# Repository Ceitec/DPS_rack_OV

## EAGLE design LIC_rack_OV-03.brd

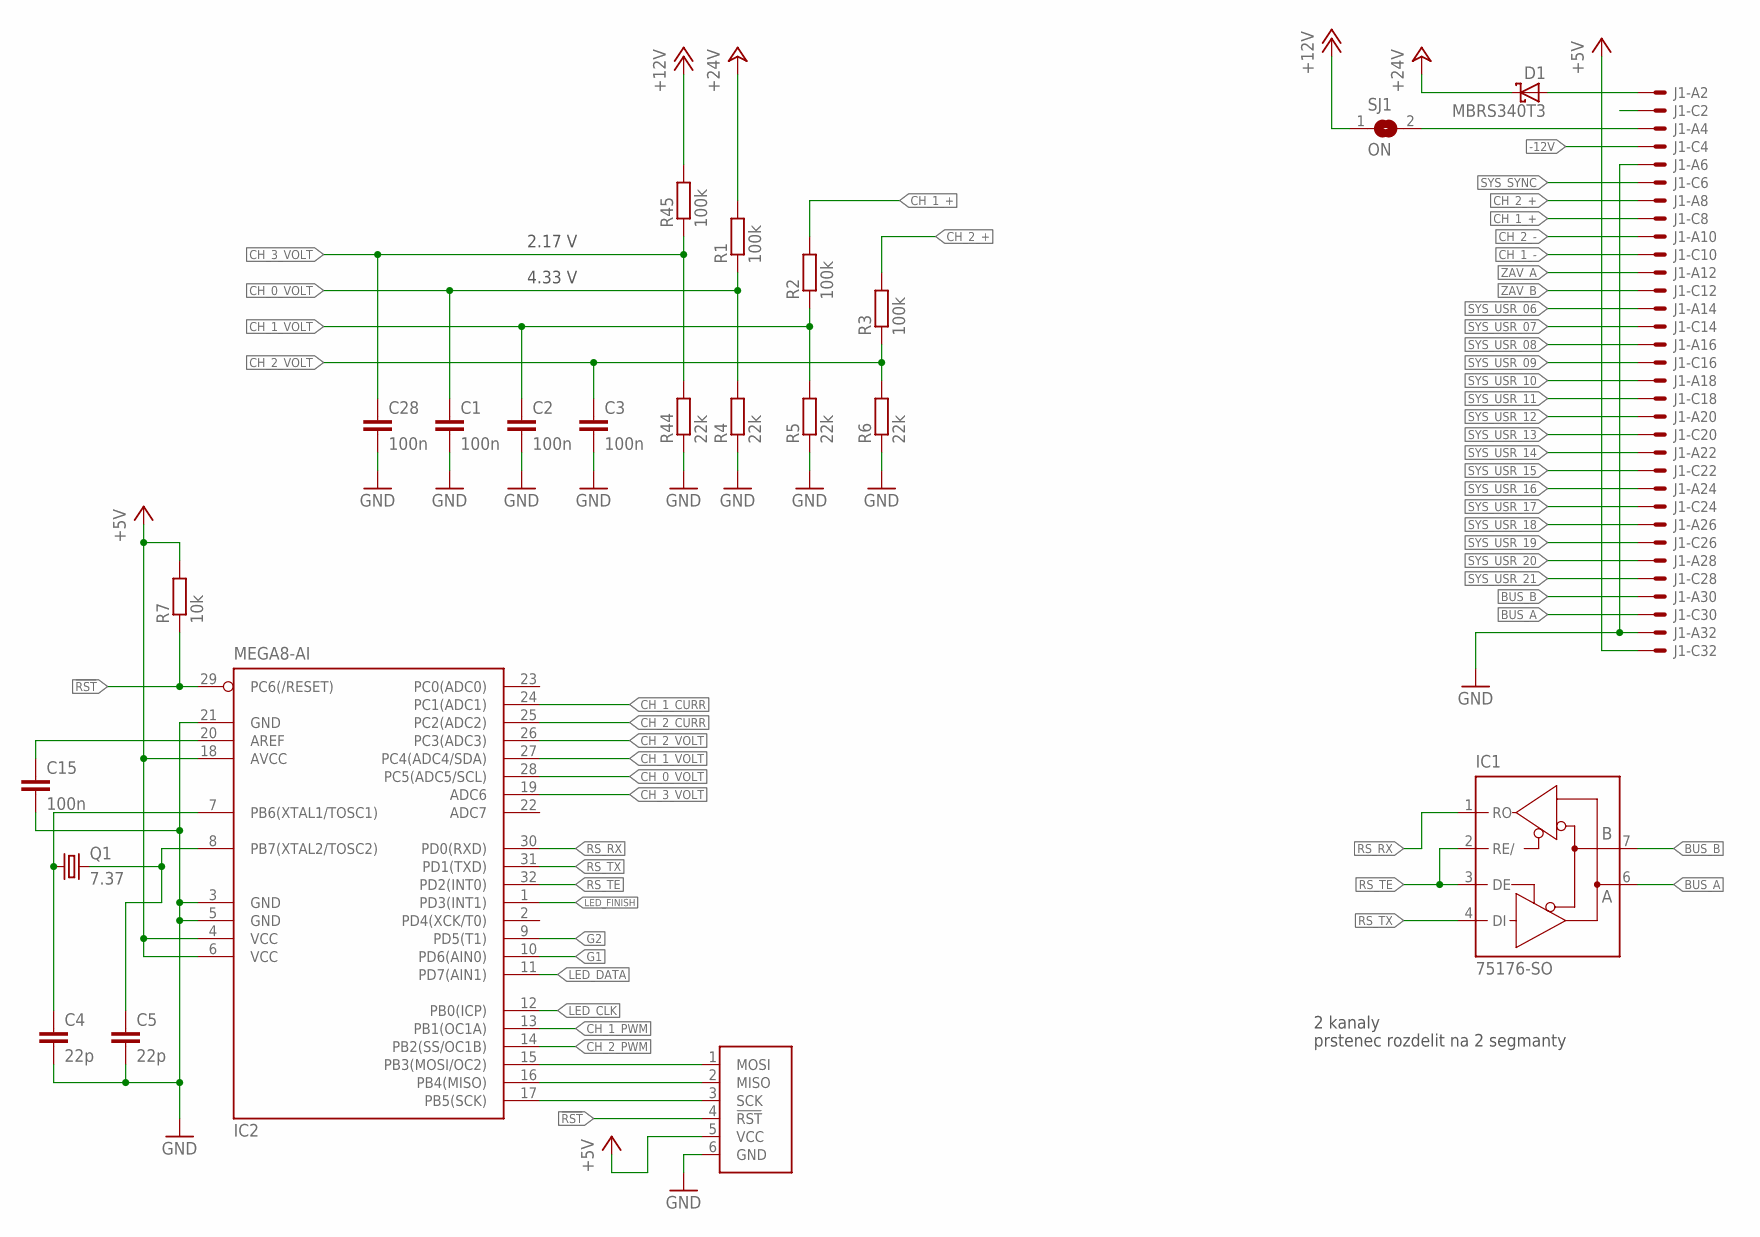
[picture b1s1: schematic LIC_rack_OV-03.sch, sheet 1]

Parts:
C1, C2, C3, C15, C28: 100n; C1206
C4, C5: 22p; C0805
D1: MBRS340T3; SMC
IC1: 75176-SO; SO08
IC2: MEGA8-AI; TQFP32-08
J1: VG32SP; VG32P
Q1: 7.37; HC49U70
R1, R2, R3, R45: 100k; R1206
R4, R5, R6, R44: 22k; R1206
R7: 10k; R1206
SJ1: ON; SJ-D
U1: ATPROG-V; 6410-06

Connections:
!RST: IC2.29 (PC6(/RESET)), R7.1, U1.4 (!RST)
+5V: IC2.4 (VCC), IC2.6 (VCC), IC2.18 (AVCC), J1.C32 (MSV), R7.2, U1.5 (VCC); also elsewhere on the board
+12V: R45.2, SJ1.1; also elsewhere on the board
+24V: D1.C, R1.2; also elsewhere on the board
+24V_D: D1.A, J1.A2 (MS)
-12V: J1.C4 (MS)
AREF: C15.1, IC2.20 (AREF)
BUS_A: IC1.6 (A), J1.C30 (MS)
BUS_B: IC1.7 (B), J1.A30 (MS)
CH_0_VOLT: C1.1, IC2.28 (PC5(ADC5/SCL)), R1.1, R4.2
CH_1_+: J1.C8 (MS), R2.2; also elsewhere on the board
CH_1_-: J1.C10 (MS); also elsewhere on the board
CH_1_CURR: IC2.24 (PC1(ADC1)); also elsewhere on the board
CH_1_PWM: IC2.13 (PB1(OC1A)); also elsewhere on the board
CH_1_VOLT: C2.1, IC2.27 (PC4(ADC4/SDA)), R2.1, R5.2
CH_2_+: J1.A8 (MS), R3.2; also elsewhere on the board
CH_2_-: J1.A10 (MS); also elsewhere on the board
CH_2_CURR: IC2.25 (PC2(ADC2)); also elsewhere on the board
CH_2_PWM: IC2.14 (PB2(SS/OC1B)); also elsewhere on the board
CH_2_VOLT: C3.1, IC2.26 (PC3(ADC3)), R3.1, R6.2
CH_3_VOLT: C28.1, IC2.19 (ADC6), R44.2, R45.1
G1: IC2.10 (PD6(AIN0)); also elsewhere on the board
G2: IC2.9 (PD5(T1)); also elsewhere on the board
GND: C1.2, C2.2, C3.2, C4.2, C5.2, C15.2, C28.2, IC2.3 (GND), IC2.5 (GND), IC2.21 (GND), J1.A6 (MS), J1.A32 (MS), R4.1, R5.1, R6.1, R44.1, U1.6 (GND); also elsewhere on the board
LED_CLK: IC2.12 (PB0(ICP)); also elsewhere on the board
LED_DATA: IC2.11 (PD7(AIN1)); also elsewhere on the board
LED_FINISH: IC2.1 (PD3(INT1)); also elsewhere on the board
PROG_MISO: IC2.16 (PB4(MISO)), U1.2 (MISO)
PROG_MOSI: IC2.15 (PB3(MOSI/OC2)), U1.1 (MOSI)
PROG_SCK: IC2.17 (PB5(SCK)), U1.3 (SCK)
RS_RX: IC1.1 (RO), IC2.30 (PD0(RXD))
RS_TE: IC1.2 (RE/), IC1.3 (DE), IC2.32 (PD2(INT0))
RS_TX: IC1.4 (DI), IC2.31 (PD1(TXD))
SYS_12V: J1.A4 (MS), SJ1.2
SYS_+5V_NC: J1.C2 (MS)
SYS_SYNC: J1.C6 (MS)
SYS_USR_06: J1.A14 (MS)
SYS_USR_07: J1.C14 (MS)
SYS_USR_08: J1.A16 (MS)
SYS_USR_09: J1.C16 (MS)
SYS_USR_10: J1.A18 (MS)
SYS_USR_11: J1.C18 (MS)
SYS_USR_12: J1.A20 (MS)
SYS_USR_13: J1.C20 (MS)
SYS_USR_14: J1.A22 (MS)
SYS_USR_15: J1.C22 (MS)
SYS_USR_16: J1.A24 (MS)
SYS_USR_17: J1.C24 (MS)
SYS_USR_18: J1.A26 (MS)
SYS_USR_19: J1.C26 (MS)
SYS_USR_20: J1.A28 (MS)
SYS_USR_21: J1.C28 (MS)
XTAL1: C4.1, IC2.7 (PB6(XTAL1/TOSC1)), Q1.1
XTAL2: C5.1, IC2.8 (PB7(XTAL2/TOSC2)), Q1.2
ZAV_A: J1.A12 (MS); also elsewhere on the board
ZAV_B: J1.C12 (MS); also elsewhere on the board

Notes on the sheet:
2 kanaly
prstenec rozdelit na 2 segmanty
4.33 V
2.17 V

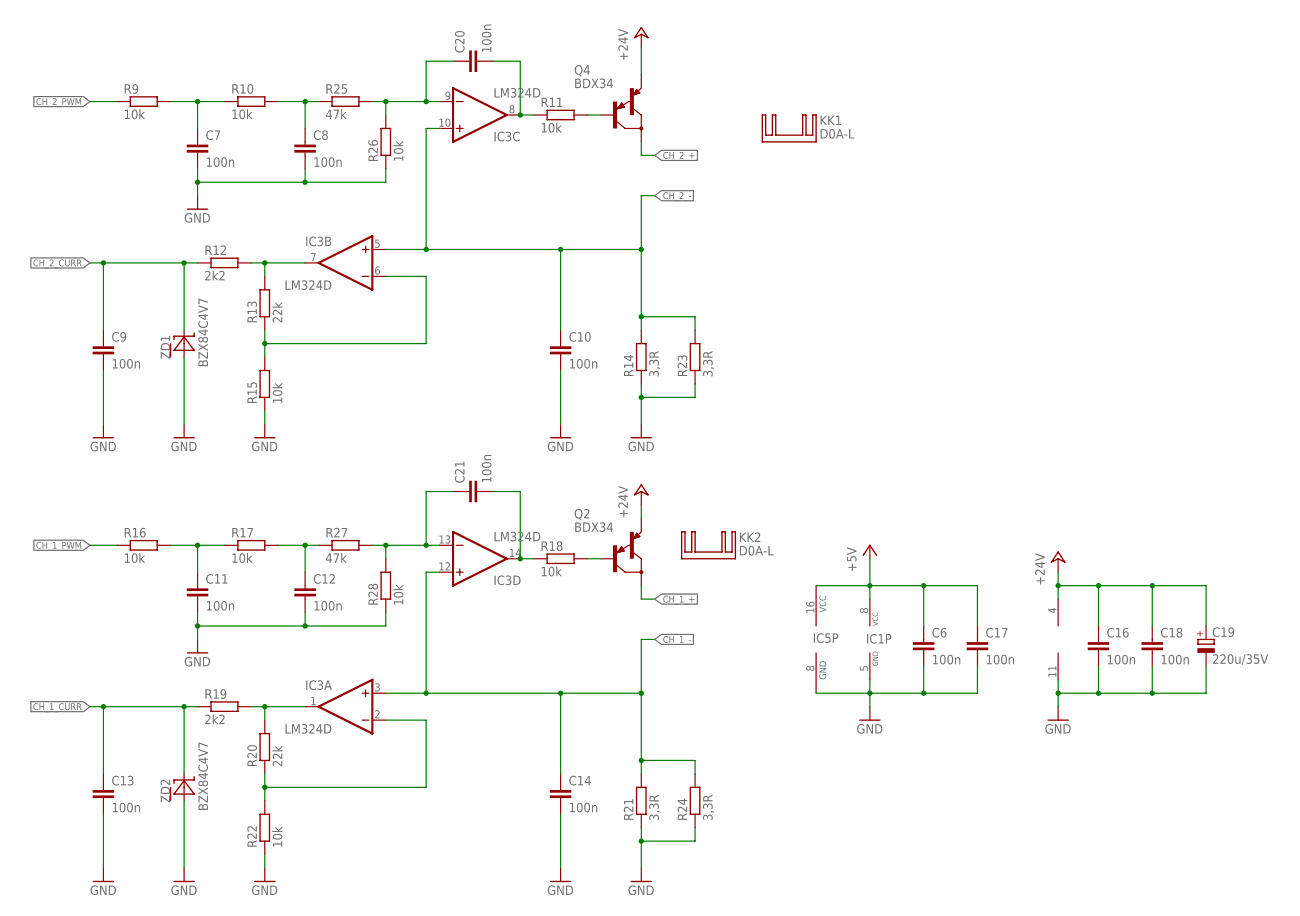
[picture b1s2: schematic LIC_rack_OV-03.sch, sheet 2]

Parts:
C6, C7, C8, C9, C10, C11, C12, C13, C14, C16, C17, C18, C20, C21: 100n; C1206
C19: 220u/35V; E3,5-8LR
IC1: 75176-SO; SO08
IC3: LM324D; SO14
IC5: 74LS595D; SO16
KK1, KK2: D0A-L; D02A-L
Q2, Q4: BDX34; TO220
R9, R10, R11, R15, R16, R17, R18, R22, R26, R28: 10k; R1206
R12, R19: 2k2; R1206
R13, R20: 22k; R1206
R14, R21: 3,3R; 0309/12
R23, R24: 3,3R; R1206
R25, R27: 47k; R1206
ZD1, ZD2: BZX84C4V7; SOT23

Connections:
+5V: C6.1, C17.1, IC1.8 (VCC), IC5.16 (VCC); also elsewhere on the board
+24V: C16.1, C18.1, C19.+, IC3.4 (V+), Q2.3 (E), Q4.3 (E); also elsewhere on the board
CH_1_+: Q2.2 (C); also elsewhere on the board
CH_1_-: C14.1, IC3.3 (+IN), IC3.12 (+IN), R21.2, R24.2; also elsewhere on the board
CH_1_BASE: Q2.1 (B), R18.2
CH_1_CURR: C13.1, R19.1, ZD2.3 (C); also elsewhere on the board
CH_1_CURR_HIVOLT: IC3.1 (OUT), R19.2, R20.2
CH_1_CURR_LOOP: IC3.2 (-IN), R20.1, R22.2
CH_1_DRIVE: C21.2, IC3.14 (OUT), R18.1
CH_1_FILT1: C11.1, R16.2, R17.1
CH_1_FILT2: C12.1, R17.2, R27.1
CH_1_FILT3: C21.1, IC3.13 (-IN), R27.2, R28.2
CH_1_PWM: R16.1; also elsewhere on the board
CH_2_+: Q4.2 (C); also elsewhere on the board
CH_2_-: C10.1, IC3.5 (+IN), IC3.10 (+IN), R14.2, R23.2; also elsewhere on the board
CH_2_BASE: Q4.1 (B), R11.2
CH_2_CURR: C9.1, R12.1, ZD1.3 (C); also elsewhere on the board
CH_2_CURR_HIVOLT: IC3.7 (OUT), R12.2, R13.2
CH_2_CURR_LOOP: IC3.6 (-IN), R13.1, R15.2
CH_2_DRIVE: C20.2, IC3.8 (OUT), R11.1
CH_2_FILT1: C7.1, R9.2, R10.1
CH_2_FILT2: C8.1, R10.2, R25.1
CH_2_FILT3: C20.1, IC3.9 (-IN), R25.2, R26.2
CH_2_PWM: R9.1; also elsewhere on the board
GND: C6.2, C7.2, C8.2, C9.2, C10.2, C11.2, C12.2, C13.2, C14.2, C16.2, C17.2, C18.2, C19.-, IC1.5 (GND), IC3.11 (V-), IC5.8 (GND), R14.1, R15.1, R21.1, R22.1, R23.1, R24.1, R26.1, R28.1, ZD1.1 (A), ZD2.1 (A); also elsewhere on the board

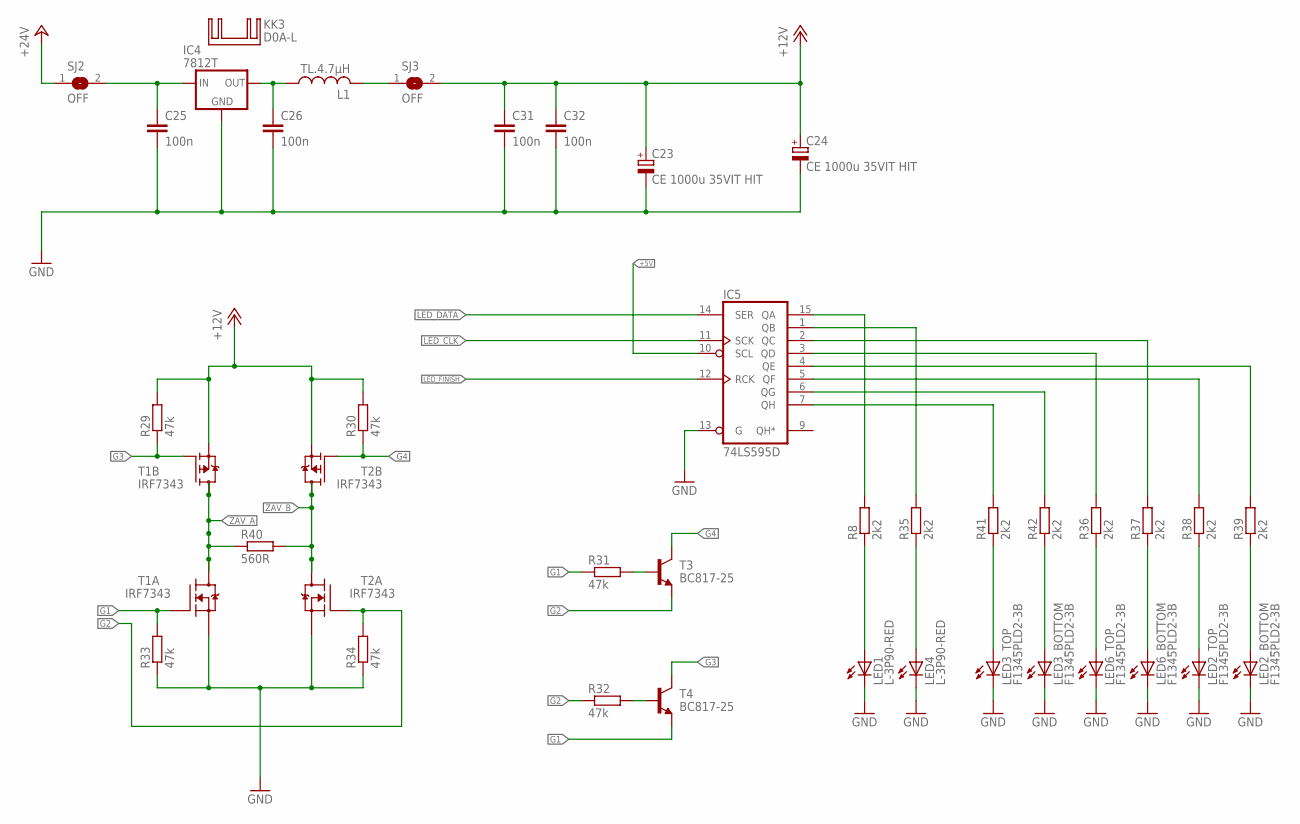
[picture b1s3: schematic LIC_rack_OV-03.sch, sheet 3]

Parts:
C23, C24: CE 1000u 35VIT HIT; E5-13X26-LR
C25, C26, C31, C32: 100n; C1206
IC4: 7812T; TO220H
IC5: 74LS595D; SO16
KK3: D0A-L; D02A-L
L1: TL.4.7µH; 0207/12
LED1, LED4: L-3P90-RED; L-3P90
LED2, LED3, LED6: F1345PLD2-3B
R8, R35, R36, R37, R38, R39, R41, R42: 2k2; R1206
R29, R30, R31, R32, R33, R34: 47k; R1206
R40: 560R; R1206
SJ2, SJ3: OFF; SJ
T1, T2: IRF7343; SO-8
T3, T4: BC817-25; SOT23-BEC

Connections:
12V_FILT: L1.2, SJ3.1
12V_STAB: C26.1, IC4.3 (VO), L1.1
12V_STABIN: C25.1, IC4.1 (VI), SJ2.2
+5V: IC5.10 (SCL); also elsewhere on the board
+12V: C23.+, C24.+, C31.1, C32.1, R29.2, R30.2, SJ3.2, T1.3 (S), T2.3 (S); also elsewhere on the board
+24V: SJ2.1; also elsewhere on the board
G1: R31.1, R33.2, T1.2 (G), T4.E; also elsewhere on the board
G1_B: R31.2, T3.B
G2: R32.1, R34.2, T2.2 (G), T3.E; also elsewhere on the board
G2_B: R32.2, T4.B
G3: R29.1, T1.4 (G), T4.C
G4: R30.1, T2.4 (G), T3.C
GND: C23.-, C24.-, C25.2, C26.2, C31.2, C32.2, IC4.2 (GND), IC5.13 (G), LED1.K (C), LED2.1K (C), LED2.2K (C), LED3.1K (C), LED3.2K (C), LED4.K (C), LED6.1K (C), LED6.2K (C), R33.1, R34.1, T1.1 (S), T2.1 (S); also elsewhere on the board
LED_ACT: IC5.1 (QB), R35.2
LED_ACT_R: LED4.A, R35.1
LED_CLK: IC5.11 (SCK); also elsewhere on the board
LED_DATA: IC5.14 (SER); also elsewhere on the board
LED_FINISH: IC5.12 (RCK); also elsewhere on the board
LED_OK: IC5.15 (QA), R8.2
LED_OK_R: LED1.A, R8.1
LED_OSV1_GREEN: IC5.7 (QH), R41.2
LED_OSV1_GREEN_R: LED3.2A (A), R41.1
LED_OSV1_RED: IC5.6 (QG), R42.2
LED_OSV1_RED_R: LED3.1A (A), R42.1
LED_OSV2_GREEN: IC5.3 (QD), R36.2
LED_OSV2_GREEN_R: LED6.2A (A), R36.1
LED_OSV2_RED: IC5.2 (QC), R37.2
LED_OSV2_RED_R: LED6.1A (A), R37.1
LED_ZAV_GREEN: IC5.5 (QF), R38.2
LED_ZAV_GREEN_R: LED2.2A (A), R38.1
LED_ZAV_RED: IC5.4 (QE), R39.2
LED_ZAV_RED_R: LED2.1A (A), R39.1
ZAV_A: R40.1, T1.5 (D), T1.6 (D1), T1.7 (D), T1.8 (D1); also elsewhere on the board
ZAV_B: R40.2, T2.5 (D), T2.6 (D1), T2.7 (D), T2.8 (D1); also elsewhere on the board

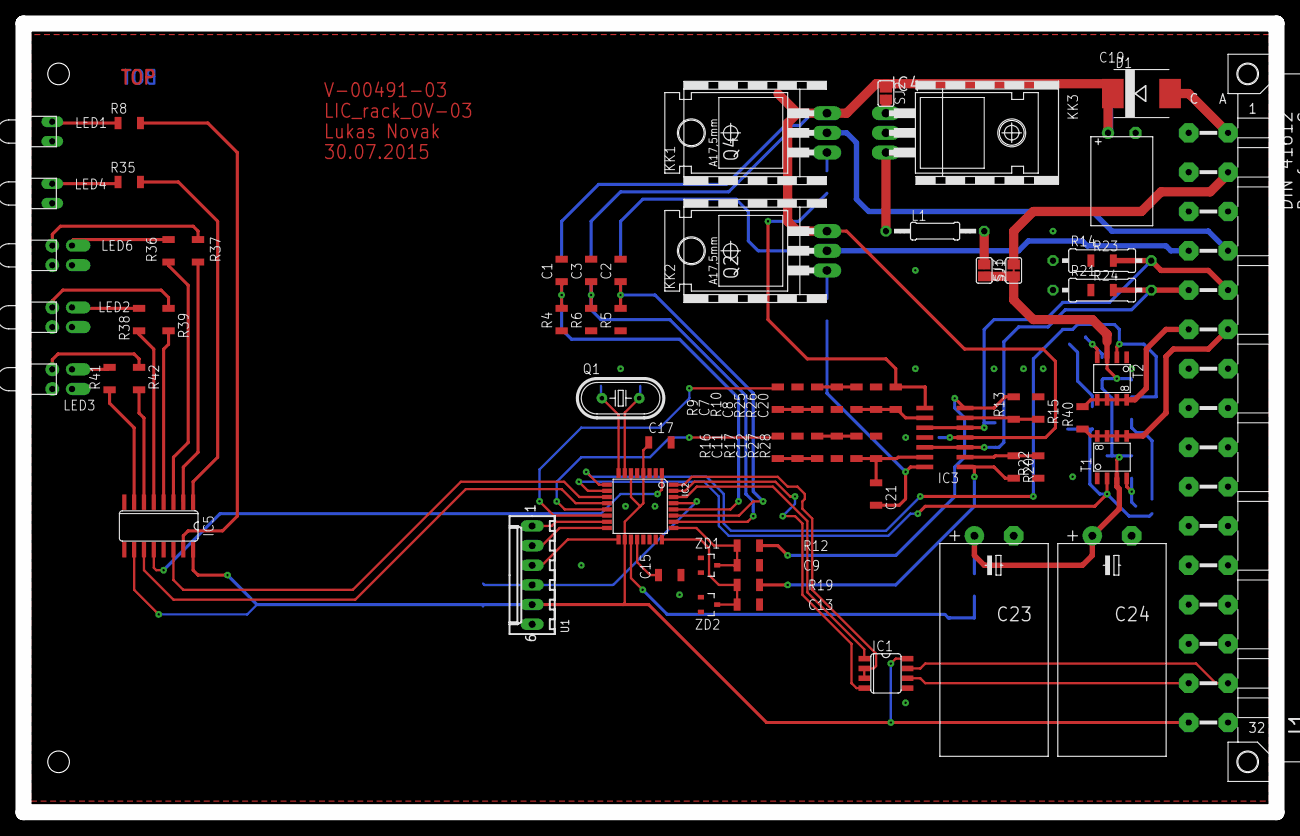
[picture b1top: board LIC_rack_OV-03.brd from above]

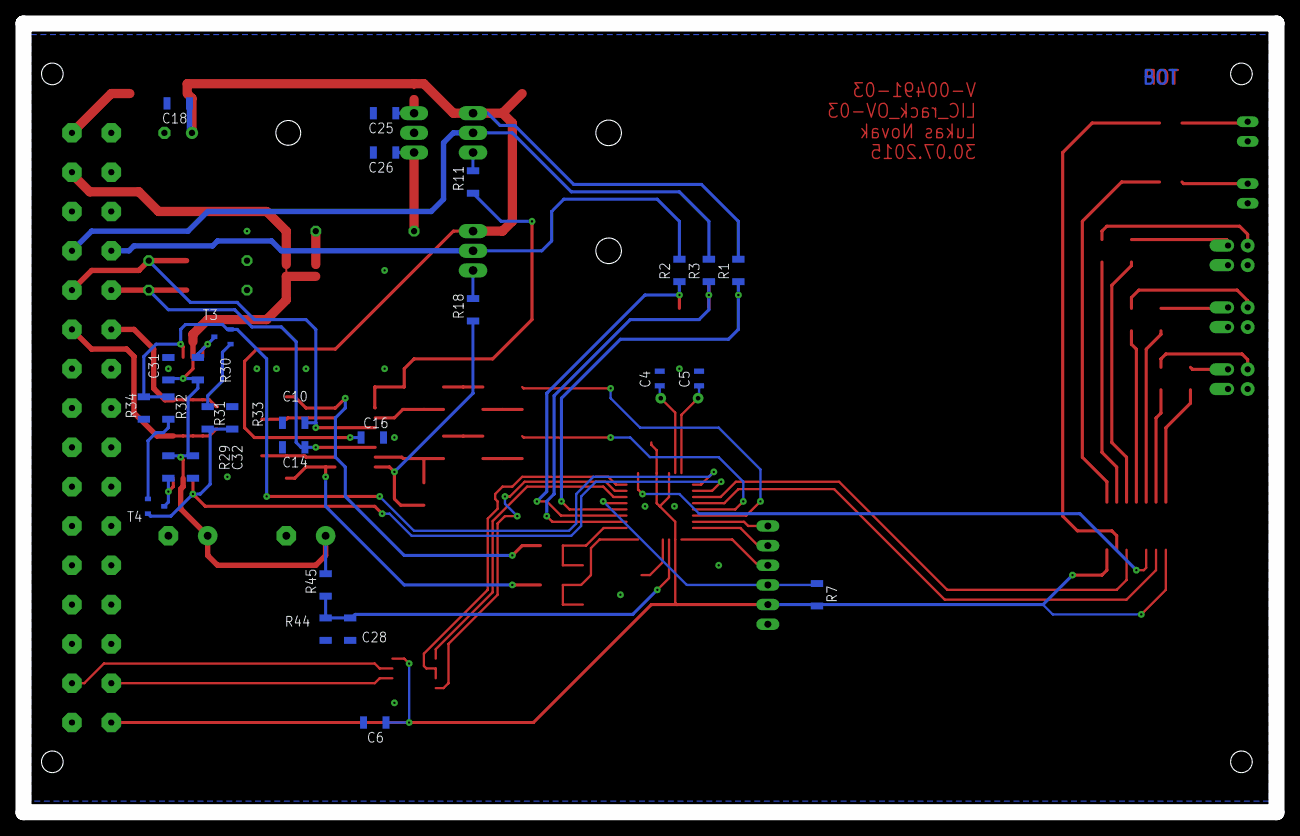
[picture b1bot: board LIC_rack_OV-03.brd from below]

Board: 2 copper layers, 162.0 x 102.0 mm, 101 parts (28 on the bottom side), 74 nets.

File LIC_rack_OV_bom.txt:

Partlist exported from D:/Michal/Elektronika/projekty/VUT/LIBS_Tescan/DPS_rack_OV/LIC_rack_OV.sch at 18.6.2014 19:04:13

Qty Value      Device         Parts                                                                   GM                 code   
1              VG32SP         J1                                                                                                
1   1R         R-EU_0309/12   R21                                                                                               
3   2k2        R-EU_R1206     R8, R12, R19                                                            R1206 2k2          900-197
1   3,3R       R-EU_0309/12   R14                                                                                               
2   3,3R       R-EU_R1206     R23, R24                                                                                          
1   7.37       XTAL           Q1                                                                                                
11  10k        R-EU_R1206     R7, R9, R10, R11, R15, R16, R17, R18, R22, R26, R28                     R1206 10K 1%       900-179
5   22k        R-EU_R1206     R4, R5, R6, R13, R20                                                    R1206 22K 1%       900-224
2   22p        C-EUC0805      C4, C5                                                                  CK0805 22P/50V NPO 906-079
2   47k        R-EU_R1206     R25, R27                                                                R1206 47K 1%       900-116
3   100k       R-EU_R1206     R1, R2, R3                                                              R1206 100K 1%      900-002
16  100n       C-EUC1206      C1, C2, C3, C6, C7, C8, C9, C10, C11, C12, C13, C14, C15, C16, C17, C18 CK 1206 100nF      -      
1   220u/35V   CPOL-EUE3.5-8L C19                                                                                               
1   75176-SO   75176-SO       IC1                                                                     75176 SMD          959-001
1   ATPROG-V   ATPROG-V       U1                                                                                                
2   BDX34      BDX34          Q2, Q4                                                                                            
2   BZX84C4V7  BZX84C4V7      ZD1, ZD2                                                                                          
2   D0A-L      D0A-L          KK1, KK2                                                                                          
1   L-3P90-RED L-3P90-RED     LED1                                                                                              
1   LM324D     LM324D         IC3                                                                     LM324D SMD         925-002
1   MEGA8-AI   MEGA8-AI       IC2                                                                     ATmega8-16AU       958-102

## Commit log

2015-08-11 :confetti_ball: Added .gitattributes & .gitignore files
2015-08-11 Ovládání světel
2015-09-25 A
    A
2015-11-10 Další verze OV
